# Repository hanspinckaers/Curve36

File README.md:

# About

This is a diodeless, 36 key, split (reversible PCB), wireless keyboard with Choc V1 switches, based off of the [Keiler](https://github.com/jonathanforking/Keiler) 

Everything has splay, including the index finger. Some columns are slightly curved to follow the movement my fingers make while typing.

I'm not super happy with the amount of underreach the innermost thumb key has.

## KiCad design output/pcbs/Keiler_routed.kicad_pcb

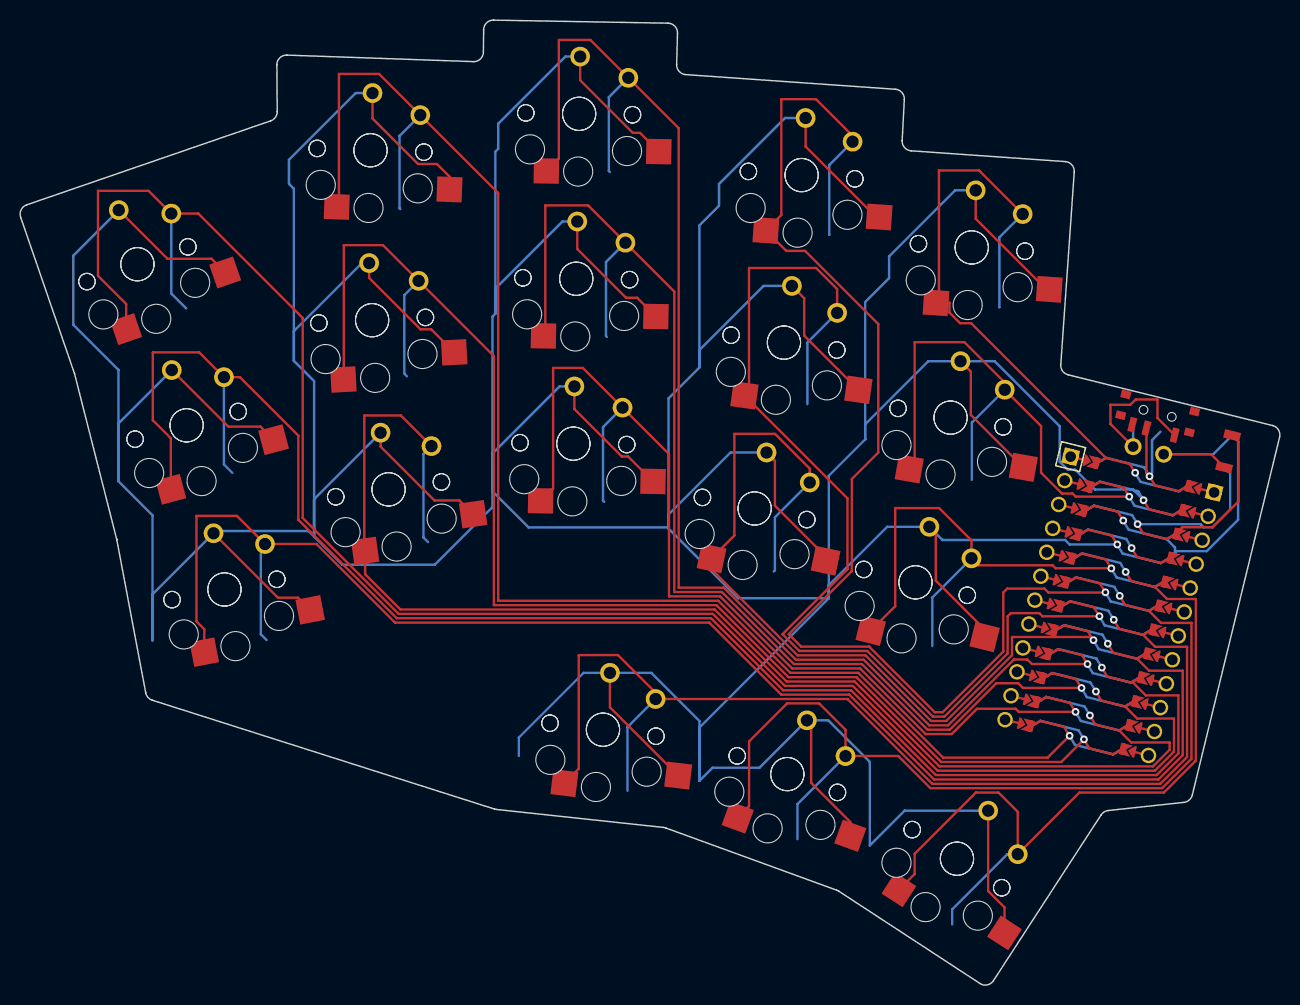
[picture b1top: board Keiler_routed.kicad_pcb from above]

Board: 2 copper layers, 129.8 x 99.5 mm, 37 parts (0 on the bottom side), 19 nets.

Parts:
MCU1: ProMicro
S1, S2, S3, S4, S5, S6, S7, S8, S9, S10, S11, S12, S13, S14, S15, S16, S17, S18, S19, S20, S21, S22, S23, S24, S25, S26, S27, S28, S29, S30, S31, S32, S33, S34, S35, S36: PG1350

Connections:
GND: MCU1.2, MCU1.21, MCU1.22, S1.2, S2.2, S3.2, S4.2, S5.2, S6.2, S7.2, S8.2, S9.2, S10.2, S11.2, S12.2, S13.2, S14.2, S15.2, S16.2, S17.2, S18.2, S19.2, S20.2, S21.2, S22.2, S23.2, S24.2, S25.2, S26.2, S27.2, S28.2, S29.2, S30.2, S31.2, S32.2, S33.2, S34.2, S35.2, S36.2
P0: MCU1.23, S14.1, S32.1
P1: MCU1.24, S15.1, S33.1
P2: MCU1.20, S13.1, S31.1
P3: MCU1.19, S12.1, S30.1
P4: MCU1.18, S11.1, S29.1
P5: MCU1.17, S10.1, S28.1
P6: MCU1.16, S9.1, S27.1
P7: MCU1.15, S8.1, S26.1
P8: MCU1.14, S7.1, S25.1
P9: MCU1.13, S6.1, S24.1
P10: MCU1.12, S5.1, S23.1
P14: MCU1.10, S3.1, S21.1
P15: MCU1.9, S2.1, S20.1
P16: MCU1.11, S4.1, S22.1
P18: MCU1.8, S1.1, S19.1
P19: MCU1.7, S16.1, S34.1
P20: MCU1.6, S17.1, S35.1
P21: MCU1.5, S18.1, S36.1

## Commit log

2024-03-16 fix(promicro_pretty.js):replace p.xy with p.eaxy due to update of ergogen
2024-05-21 removed artifacts
2024-05-22 Updated gitignore
2024-05-22 Updated switch layout
2024-05-22 Added build script
2024-05-22 Updated pcb
2024-05-22 Added TODOs
2024-05-22 Mounting + Plate fix
2024-05-22 Update TODO
2024-05-22 Updated TODO
2024-05-23 Updated mounting
2024-05-23 Added build dependency
2024-05-23 Updated TODOs
2024-05-23 Removed old gerber artefacts
2024-05-23 Removed duplicate VIAs
2024-05-23 Changed pcb name
2024-05-24 Removed mounting hole for track space
2024-05-24 Added gerbers
2024-05-24 Replaced switchplate gerbers
2024-05-25 Nicer routing
2024-05-25 Added kicad files
2024-05-25 Updated case + Added artefacts
2024-05-25 Updated case
2024-06-16 Case adjustments
2024-07-02 Added images
2024-07-02 Added firmware link
2024-07-13 Added build instructions
2024-07-13 Added bill of materials
2024-11-09 new layout
2024-11-09 remove old gerbers
